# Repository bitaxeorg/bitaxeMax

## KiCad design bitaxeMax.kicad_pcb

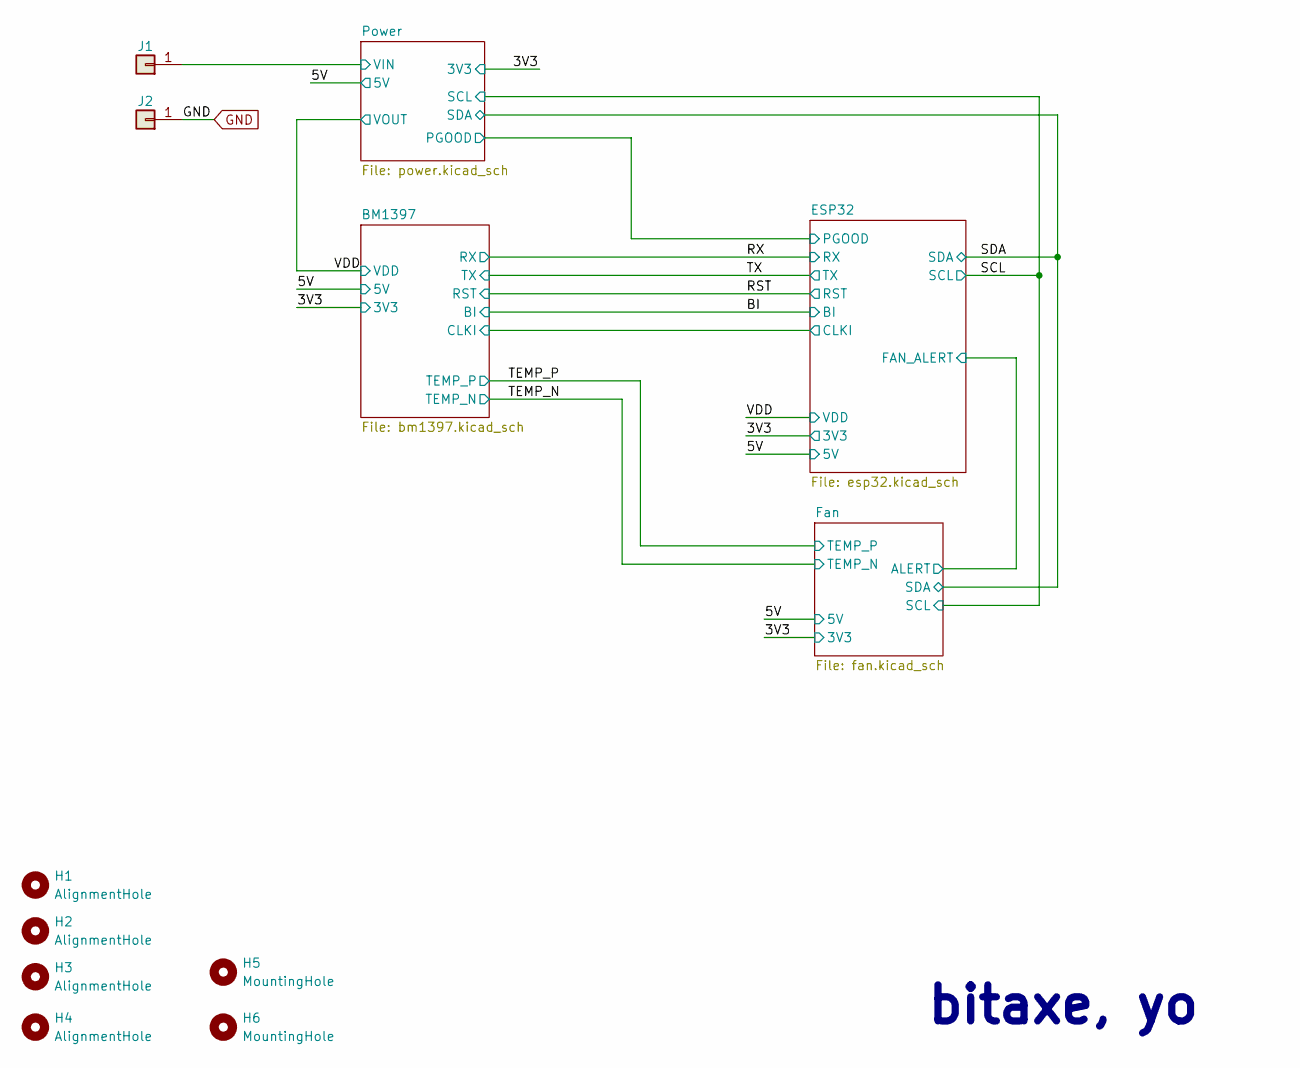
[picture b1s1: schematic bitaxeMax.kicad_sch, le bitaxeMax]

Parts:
H1, H2, H3, H4: AlignmentHole; MountingHole_2.2mm_M2
H5, H6: MountingHole; MountingHole_3.5mm
J1, J2: Conn_01x01; 63862-1; PARTNO 63862-1

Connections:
/Power/VIN: J1.1; also elsewhere on the board
GND: J2.1; also elsewhere on the board

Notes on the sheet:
bitaxe, yo

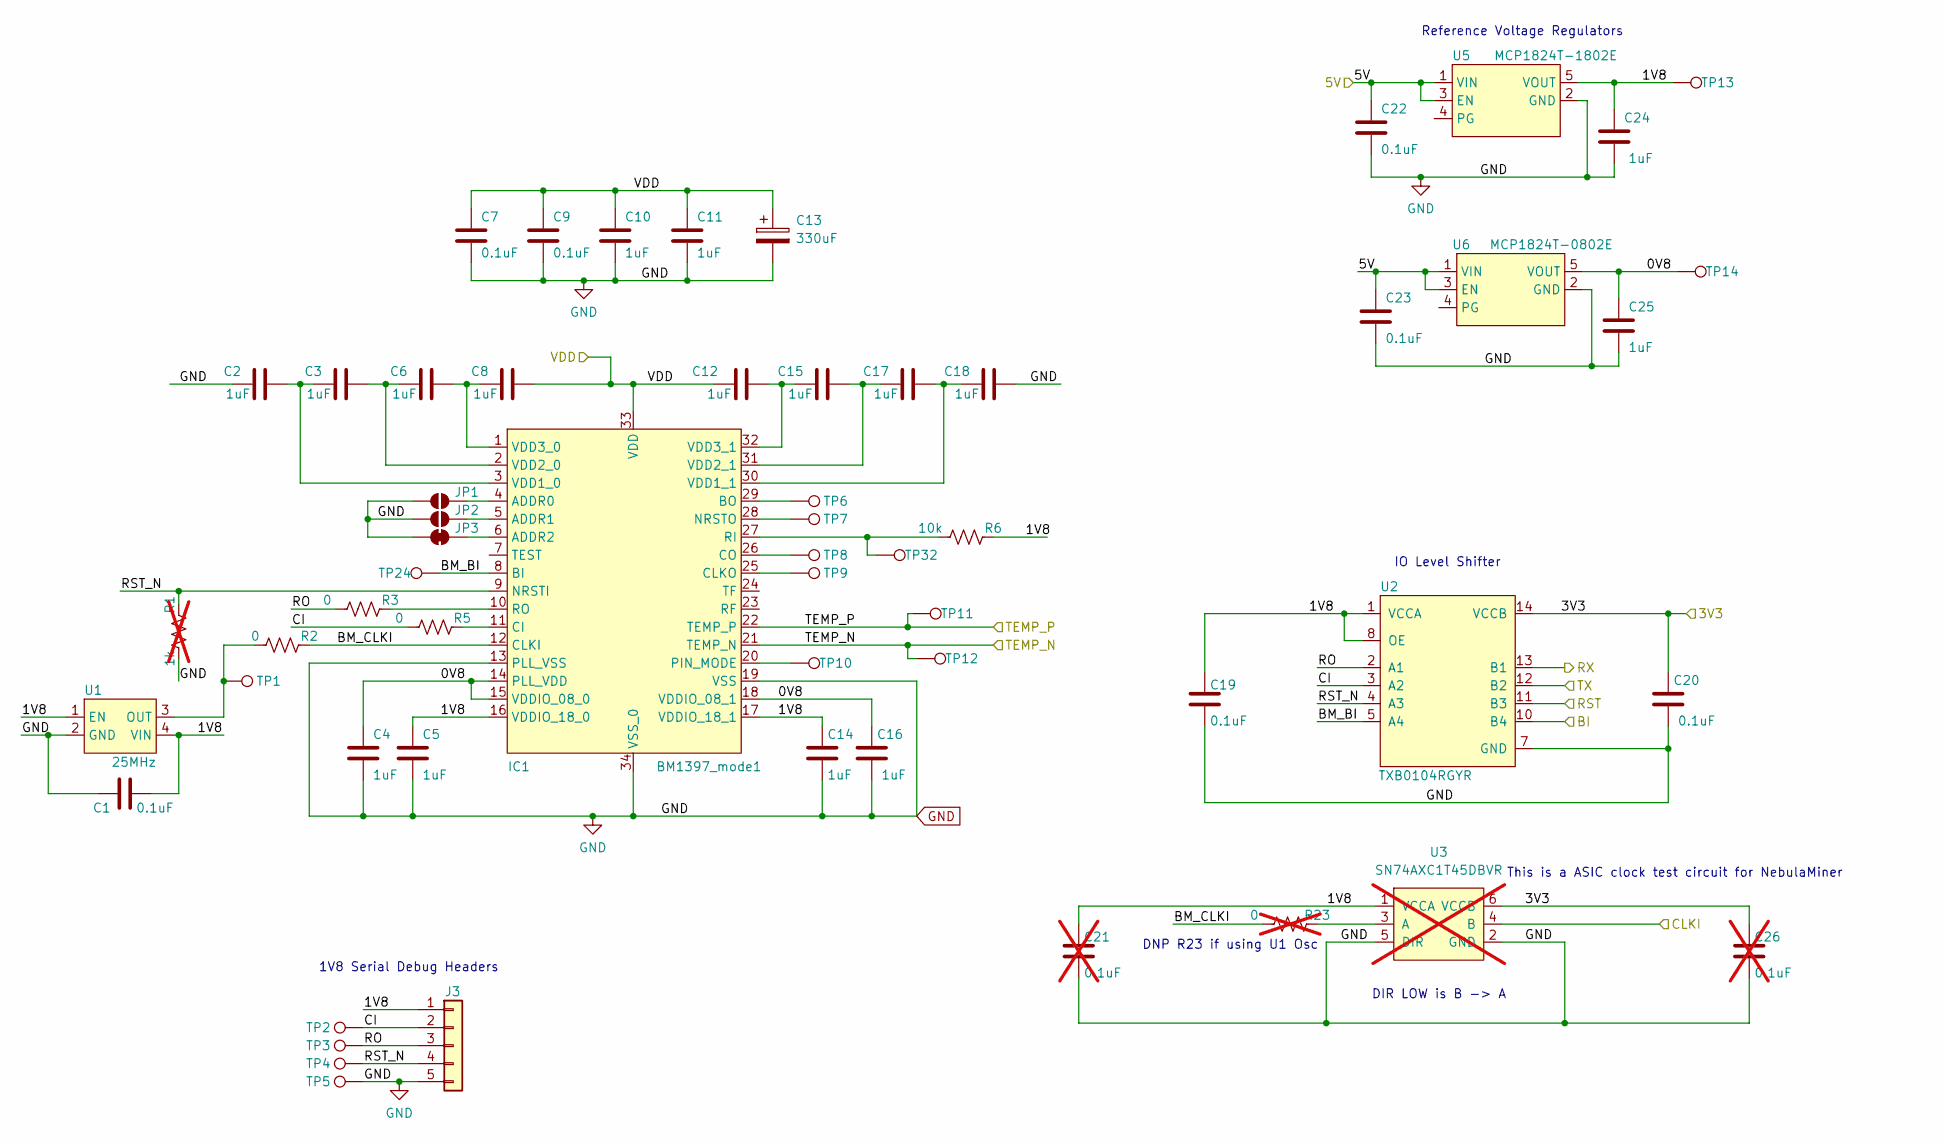
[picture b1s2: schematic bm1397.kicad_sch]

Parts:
C1, C7, C9, C19, C20, C22, C23: 0.1uF; C_0402_1005Metric; PARTNO 0402X104K100CT
C2, C3, C4, C5, C6, C8, C10, C11, C12, C14, C15, C16, C17, C18, C24, C25: 1uF; C_0402_1005Metric; PARTNO EMK105BJ105MV-F
C13: 330uF; CP_EIA-7343-31_Kemet-D_Pad2.25x2.55mm_HandSolder; PARTNO 293D337X9010E2TE3
C21, C26: 0.1uF; C_0402_1005Metric; PARTNO 0402X104K100CT; not fitted
IC1: BM1397_mode1; BM1397
J3: Conn_01x05; PinHeader_1x05_P2.54mm_Vertical
JP1, JP2: SolderJumper_2_Open; SolderJumper-2_P1.3mm_Open_RoundedPad1.0x1.5mm
JP3: SolderJumper_2_Bridged; SolderJumper-2_P1.3mm_Bridged2Bar_RoundedPad1.0x1.5mm
R1: 1k; R_0402_1005Metric; not fitted
R2, R3, R5: 0; R_0402_1005Metric; PARTNO RMCF0402ZT0R00
R6: 10k; R_0402_1005Metric; PARTNO RC0402JR-0710KL
R23: 0; R_0402_1005Metric; PARTNO RMCF0402ZT0R00; not fitted
TP1, TP2, TP3, TP4, TP5, TP6, TP7, TP8, TP9, TP10, TP11, TP12, TP13, TP14, TP24, TP32: TestPoint; TestPoint_Pad_D1.5mm
U1: 25MHz; O 25,0-JO32-B-1V3-1-T1-LF; PARTNO O 25,0-JO32-B-1V3-1-T1-LF
U2: TXB0104RGYR; TXB0104; PARTNO TXB0104RGYR
U3: SN74AXC1T45DBVR; SN74AXC1T45; PARTNO SN74AXC1T45DBVR; not fitted
U5: MCP1824T-1802E; SOT-23-5; PARTNO MCP1824T-1802E/OT
U6: MCP1824T-0802E; SOT-23-5; PARTNO MCP1824T-0802E/OT

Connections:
/3V3: C20.1, C26.1, U2.14 (VCCB), U3.6 (VCCB); also elsewhere on the board
/5V: C22.1, C23.1, U5.1 (VIN), U5.3 (EN), U6.1 (VIN), U6.3 (EN); also elsewhere on the board
/BI: U2.10 (B4); also elsewhere on the board
/BM1397/0V8: C4.1, C16.1, C25.1, IC1.14 (PLL_VDD), IC1.15 (VDDIO_08_0), IC1.18 (VDDIO_08_1), TP14.1, U6.5 (VOUT)
/BM1397/1V8: C1.2, C5.1, C14.1, C19.1, C21.1, C24.1, IC1.16 (VDDIO_18_0), IC1.17 (VDDIO_18_1), J3.1, R6.2, TP13.1, U1.1 (EN), U1.4 (VIN), U2.1 (VCCA), U2.8 (OE), U3.1 (VCCA), U5.5 (VOUT)
/BM1397/BM_BI: IC1.8 (BI), TP24.1, U2.5 (A4)
/BM1397/BM_CLKI: IC1.12 (CLKI), R2.2, R23.1
/BM1397/CI: J3.2, R5.1, TP2.1, U2.3 (A2)
/BM1397/CLKI: U3.4 (B); also elsewhere on the board
/BM1397/RO: J3.3, R3.1, TP3.1, U2.2 (A1)
/BM1397/RST_N: IC1.9 (NRSTI), J3.4, R1.2, TP4.1, U2.4 (A3)
/RST: U2.11 (B3); also elsewhere on the board
/RX: U2.13 (B1); also elsewhere on the board
/TEMP_N: IC1.21 (TEMP_N), TP12.1; also elsewhere on the board
/TEMP_P: IC1.22 (TEMP_P), TP11.1; also elsewhere on the board
/TX: U2.12 (B2); also elsewhere on the board
/VDD: C7.1, C8.2, C9.1, C10.1, C11.1, C12.1, C13.1, IC1.33 (VDD); also elsewhere on the board
GND: C1.1, C2.1, C4.2, C5.2, C7.2, C9.2, C10.2, C11.2, C13.2, C14.2, C16.2, C18.2, C19.2, C20.2, C21.2, C22.2, C23.2, C24.2, C25.2, C26.2, IC1.13 (PLL_VSS), IC1.19 (VSS), IC1.34 (VSS_0), J3.5, JP1.1 (A), JP2.1 (A), JP3.1 (A), R1.1, TP5.1, U1.2 (GND), U2.7 (GND), U2.15 (GND), U2.16 (GND), U2.17 (GND), U2.18 (GND), U2.19 (GND), U3.2 (GND), U3.5 (DIR), U5.2 (GND), U6.2 (GND); also elsewhere on the board
unnamed: C2.2, C3.1, IC1.3 (VDD1_0)
unnamed: C3.2, C6.1, IC1.2 (VDD2_0)
unnamed: C6.2, C8.1, IC1.1 (VDD3_0)
unnamed: C12.2, C15.1, IC1.32 (VDD3_1)
unnamed: C15.2, C17.1, IC1.31 (VDD2_1)
unnamed: C17.2, C18.1, IC1.30 (VDD1_1)
unnamed: IC1.4 (ADDR0), JP1.2 (B)
unnamed: IC1.5 (ADDR1), JP2.2 (B)
unnamed: IC1.6 (ADDR2), JP3.2 (B)
unnamed: IC1.10 (RO), R3.2
unnamed: IC1.11 (CI), R5.2
unnamed: IC1.20 (PIN_MODE), TP10.1
unnamed: IC1.25 (CLKO), TP9.1
unnamed: IC1.26 (CO), TP8.1
unnamed: IC1.27 (RI), R6.1, TP32.1
unnamed: IC1.28 (NRSTO), TP7.1
unnamed: IC1.29 (BO), TP6.1
unnamed: R2.1, TP1.1, U1.3 (OUT)
unnamed: R23.2, U3.3 (A)

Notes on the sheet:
1V8 Serial Debug Headers
Reference Voltage Regulators
DNP R23 if using U1 Osc
This is a ASIC clock test circuit for NebulaMiner
IO Level Shifter
DIR LOW is B -> A

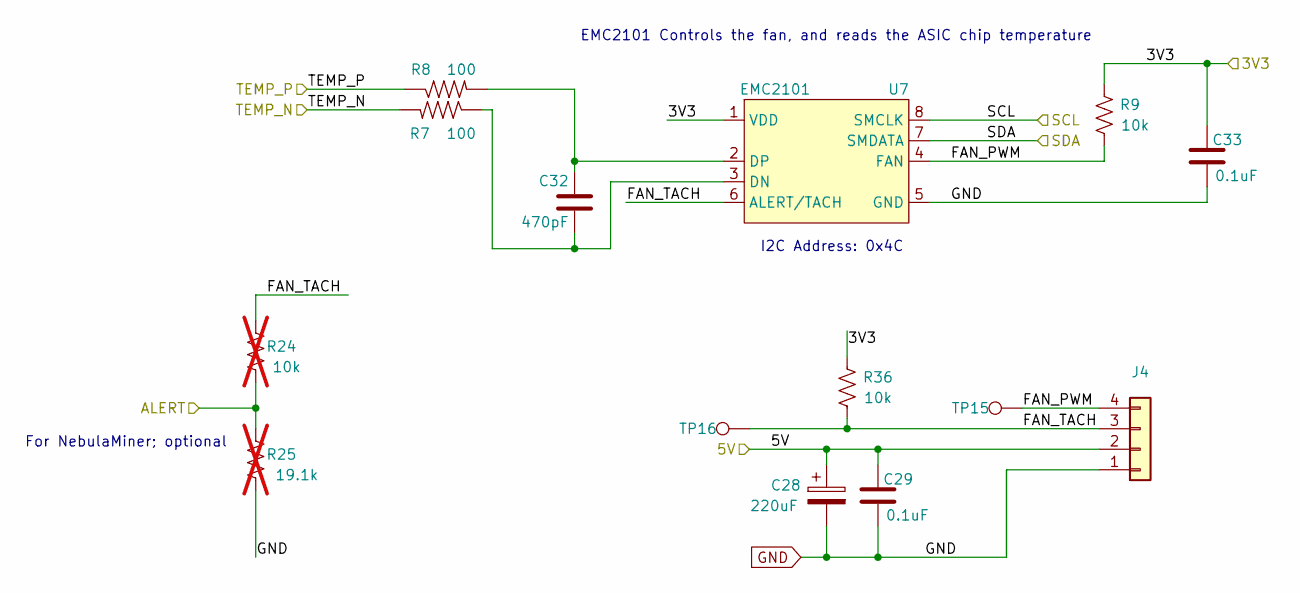
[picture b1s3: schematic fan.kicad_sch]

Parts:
C28: 220uF; CP_Elec_6.3x7.7; PARTNO 865080345012
C29, C33: 0.1uF; C_0402_1005Metric; PARTNO 0402X104K100CT
C32: 470pF; C_0402_1005Metric; PARTNO CL05B471KB5NNNC
J4: Conn_01x04; 470531000; PARTNO 0470531000
R7, R8: 100; R_0402_1005Metric; PARTNO RMCF0402FT100R
R9, R36: 10k; R_0402_1005Metric; PARTNO RC0402JR-0710KL
R24: 10k; R_0402_1005Metric; PARTNO RC0402JR-0710KL; not fitted
R25: 19.1k; R_0402_1005Metric; PARTNO RC0402FR-0719R1L; not fitted
TP15, TP16: TestPoint; TestPoint_Pad_D1.5mm
U7: EMC2101; TSSOP-8_3x3mm_P0.65mm; PARTNO EMC2101-R-ACZL-TR

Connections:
/3V3: C33.1, R9.2, R36.2, U7.1 (VDD); also elsewhere on the board
/5V: C28.1, C29.1, J4.2; also elsewhere on the board
/ESP32/FAN_ALERT: R24.1, R25.2; also elsewhere on the board
/Fan/FAN_PWM: J4.4, R9.1, TP15.1, U7.4 (FAN)
/Fan/FAN_TACH: J4.3, R24.2, R36.1, TP16.1, U7.6 (ALERT/TACH)
/SCL: U7.8 (SMCLK); also elsewhere on the board
/SDA: U7.7 (SMDATA); also elsewhere on the board
/TEMP_N: R7.2; also elsewhere on the board
/TEMP_P: R8.1; also elsewhere on the board
GND: C28.2, C29.2, C33.2, J4.1, R25.1, U7.5 (GND); also elsewhere on the board
unnamed: C32.1, R8.2, U7.2 (DP)
unnamed: C32.2, R7.1, U7.3 (DN)

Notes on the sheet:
For NebulaMiner; optional
EMC2101 Controls the fan, and reads the ASIC chip temperature
I2C Address: 0x4C

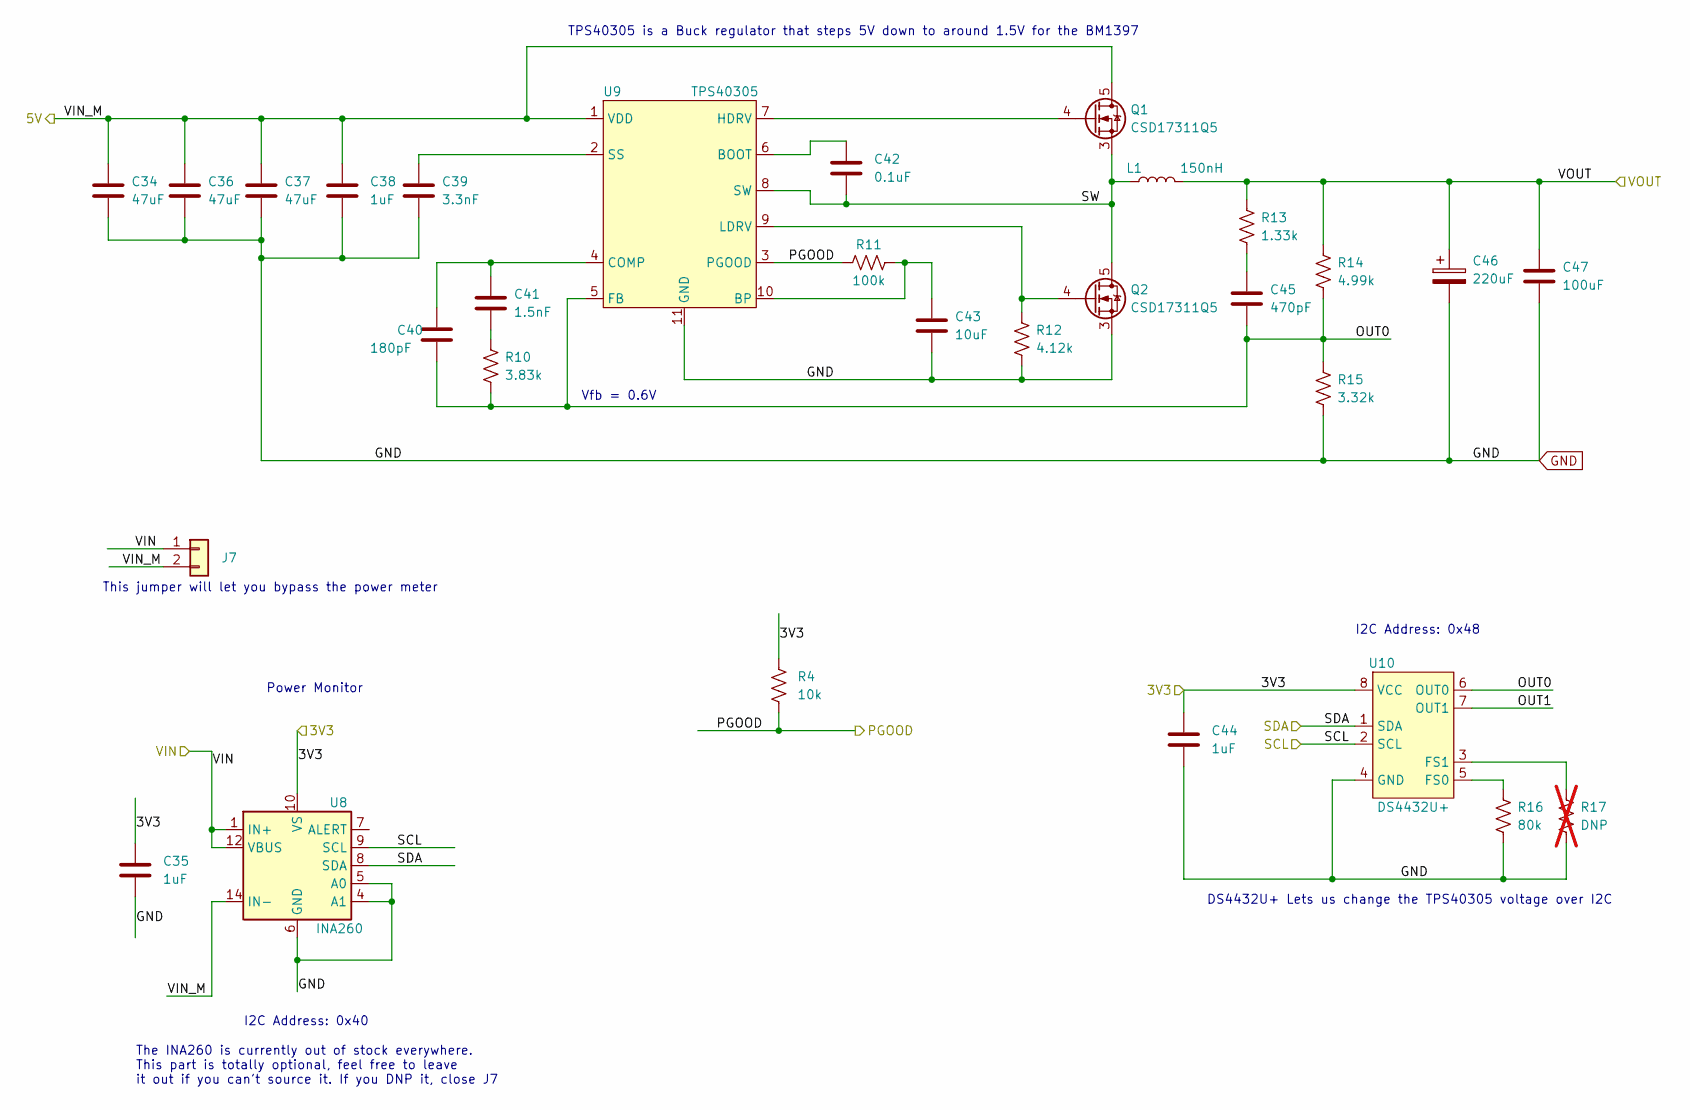
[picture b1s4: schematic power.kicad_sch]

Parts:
C34, C36, C37: 47uF; C_1210_3225Metric; PARTNO GRM32ER61C476KE15L
C35, C44: 1uF; C_0402_1005Metric; PARTNO EMK105BJ105MV-F
C38: 1uF; C_0805_2012Metric; PARTNO CL21B105KOFNNNG
C39: 3.3nF; C_0402_1005Metric; PARTNO CL05B332KB5NNNC
C40: 180pF; C_0805_2012Metric; PARTNO CC0805JRNPO9BN181
C41: 1.5nF; C_0805_2012Metric; PARTNO CC0805KRX7R9BB152
C42: 0.1uF; C_0402_1005Metric; PARTNO 0402X104K100CT
C43: 10uF; C_0805_2012Metric; PARTNO CL21A106KOQNNNE
C45: 470pF; C_0805_2012Metric; PARTNO 0805B471K500CT
C46: 220uF; CAP_2R5TPE220MAFB; PARTNO 2R5TPE220MAFB
C47: 100uF; C_1206_3216Metric; PARTNO C3216X5R0J107M160AB
J7: Conn_01x02; PinHeader_1x02_P2.54mm_Vertical
L1: 150nH; FP1005R1-R15-R; PARTNO FP1005R1-R15-R
Q1, Q2: CSD17311Q5; PARTNO CSD17311Q5
R4: 10k; R_0402_1005Metric; PARTNO RC0402JR-0710KL
R10: 3.83k; R_0402_1005Metric; PARTNO RC0402FR-073K83L
R11: 100k; R_0402_1005Metric; PARTNO RC0402JR-07100KL
R12: 4.12k; R_0402_1005Metric; PARTNO RMCF0402FT4K12
R13: 1.33k; R_0402_1005Metric; PARTNO RC0402FR-071K33L
R14: 4.99k; R_0402_1005Metric; PARTNO RC0402FR-074K99L
R15: 3.32k; R_0402_1005Metric; PARTNO RC0402FR-073K32L
R16: 80k; R_0402_1005Metric; PARTNO RC0402FR-0780K6L
R17: DNP; R_0402_1005Metric; not fitted
U8: INA260; TSSOP-16_4.4x5mm_P0.65mm; PARTNO INA260AIPWR
U9: TPS40305; PARTNO TPS40305DRCR
U10: DS4432U+; TSSOP-8_3x3mm_P0.65mm; PARTNO DS4432U+

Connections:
/3V3: C35.1, C44.1, R4.1, U8.10 (VS), U10.8 (VCC); also elsewhere on the board
/5V: C34.1, C36.1, C37.1, C38.1, J7.2, Q1.5 (D), U8.14 (IN-), U8.15 (IN-), U8.16 (IN-), U9.1 (VDD); also elsewhere on the board
/Power/OUT0: C40.2, C45.2, R10.2, R14.2, R15.1, U9.5 (FB), U10.6 (OUT0)
/Power/OUT1: U10.7 (OUT1)
/Power/PGOOD: R4.2, R11.1, U9.3 (PGOOD); also elsewhere on the board
/Power/SW: C42.2, L1.1, Q1.1, Q1.2, Q1.3 (S), Q2.5 (D), U9.8 (SW)
/Power/VIN: J7.1, U8.1 (IN+), U8.2 (IN+), U8.3 (IN+), U8.12 (VBUS); also elsewhere on the board
/SCL: U8.9 (SCL), U10.2 (SCL); also elsewhere on the board
/SDA: U8.8 (SDA), U10.1 (SDA); also elsewhere on the board
/VDD: C46.1, C47.1, L1.2, R13.1, R14.1; also elsewhere on the board
GND: C34.2, C35.2, C36.2, C37.2, C38.2, C39.2, C43.2, C44.2, C46.2, C47.2, Q2.1, Q2.2, Q2.3 (S), R12.2, R15.2, R16.2, R17.2, U8.4 (A1), U8.5 (A0), U8.6 (GND), U8.11 (GND), U9.11 (GND), U10.4 (GND); also elsewhere on the board
unnamed: C39.1, U9.2 (SS)
unnamed: C40.1, C41.1, U9.4 (COMP)
unnamed: C41.2, R10.1
unnamed: C42.1, U9.6 (BOOT)
unnamed: C43.1, R11.2, U9.10 (BP)
unnamed: C45.1, R13.2
unnamed: Q1.4 (G), U9.7 (HDRV)
unnamed: Q2.4 (G), R12.1, U9.9 (LDRV)
unnamed: R16.1, U10.5 (FS0)
unnamed: R17.1, U10.3 (FS1)

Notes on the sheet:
DS4432U+ Lets us change the TPS40305 voltage over I2C
I2C Address: 0x48
The INA260 is currently out of stock everywhere. This part is totally optional, feel free to leave it out if you can't source it. If you DNP it, close J7
Power Monitor
TPS40305 is a Buck regulator that steps 5V down to around 1.5V for the BM1397
I2C Address: 0x40
Vfb = 0.6V
This jumper will let you bypass the power meter

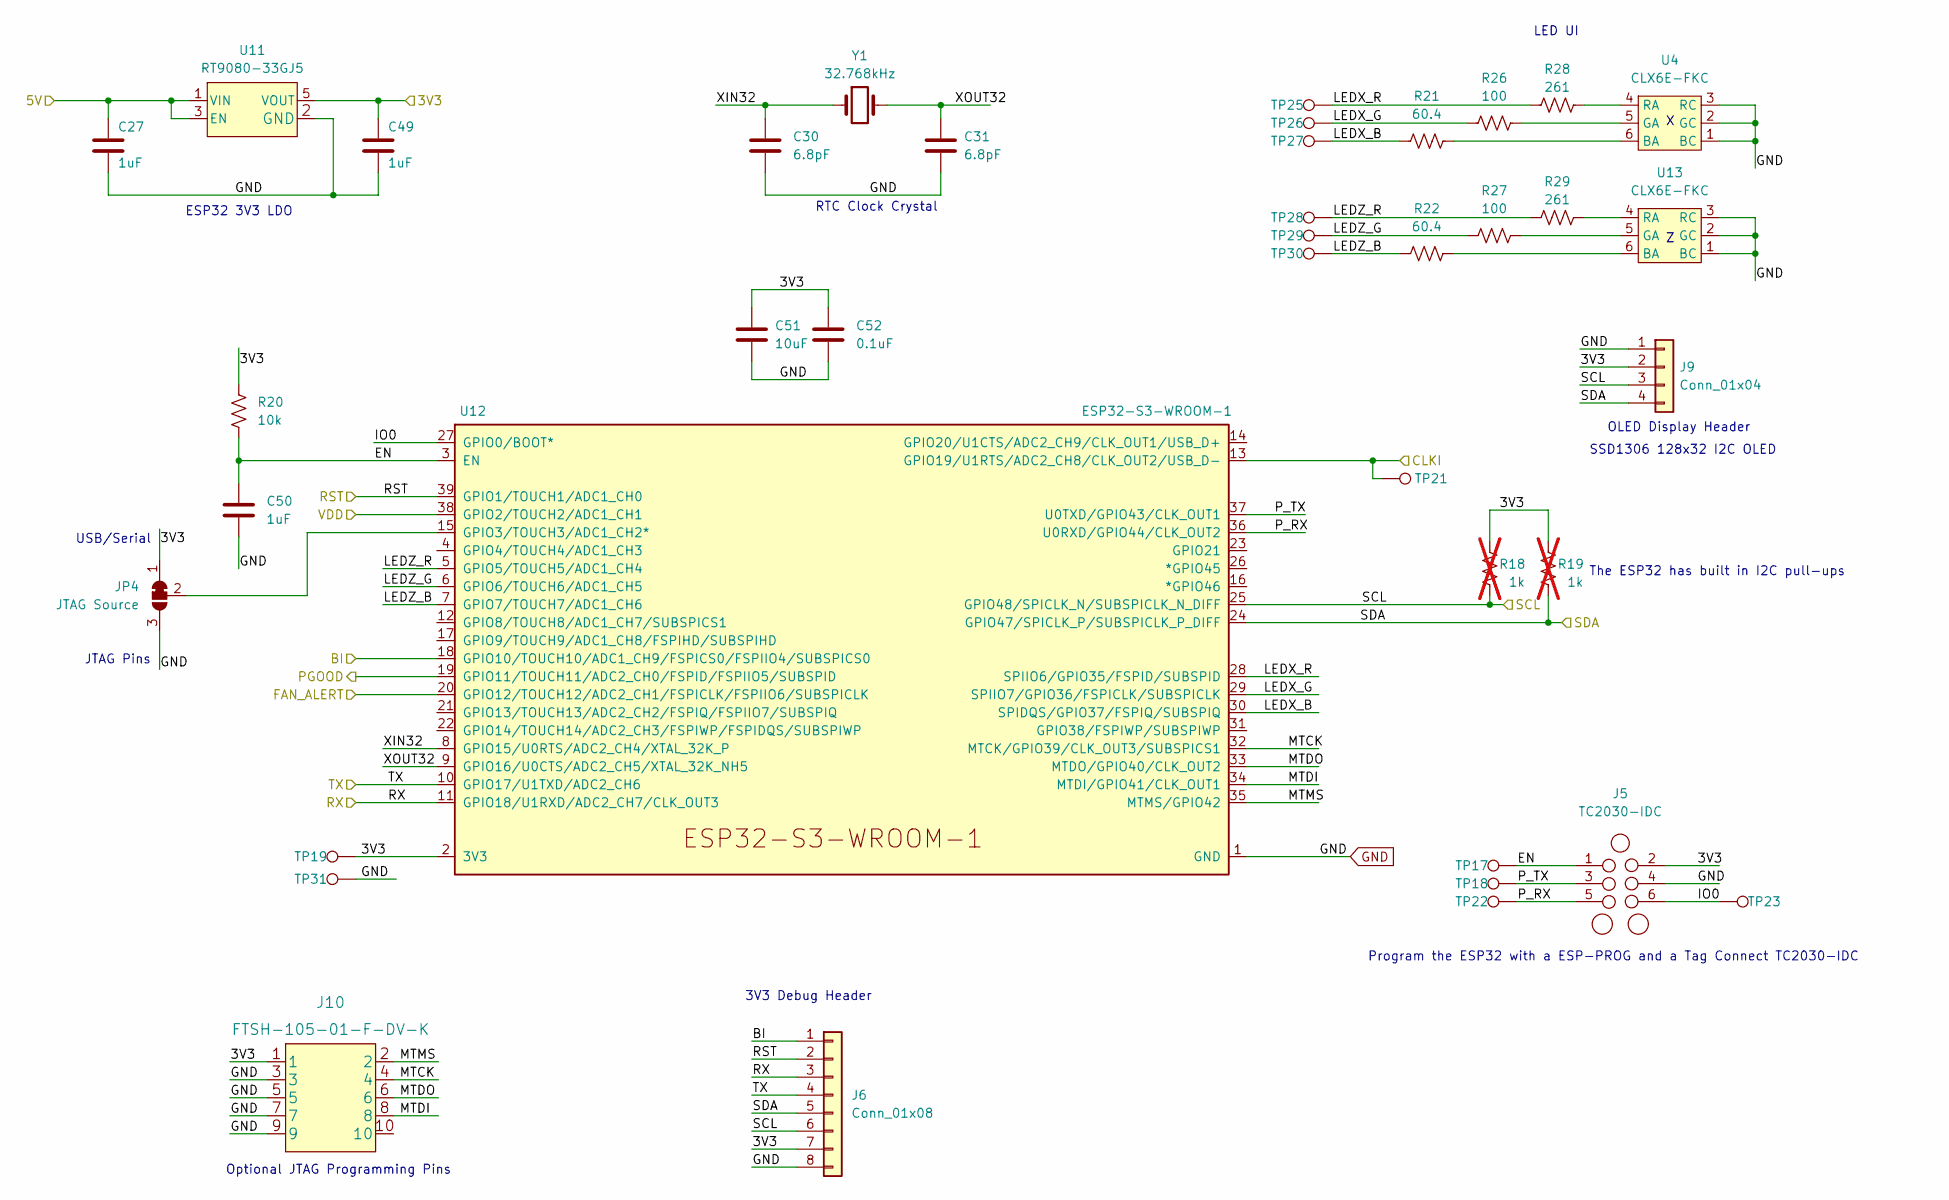
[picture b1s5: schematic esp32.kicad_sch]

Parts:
C27, C49, C50: 1uF; C_0402_1005Metric; PARTNO EMK105BJ105MV-F
C30, C31: 6.8pF; C_0402_1005Metric; PARTNO C0402C689C5GAC7867
C51: 10uF; C_0805_2012Metric; PARTNO CL21A106KOQNNNE
C52: 0.1uF; C_0402_1005Metric; PARTNO 0402X104K100CT
J5: TC2030-IDC; Tag-Connect_TC2030-IDC-NL_2x03_P1.27mm_Vertical
J6: Conn_01x08; PinHeader_1x08_P2.54mm_Vertical
J9: Conn_01x04; PinHeader_1x04_P2.54mm_Vertical
J10: FTSH-105-01-F-DV-K; PARTNO FTSH-105-01-F-DV-K
JP4: JTAG Source; SolderJumper-3_P1.3mm_Bridged2Bar12_Pad1.0x1.5mm
R18, R19: 1k; R_0402_1005Metric; not fitted
R20: 10k; R_0402_1005Metric; PARTNO RC0402JR-0710KL
R21, R22: 60.4; R_0402_1005Metric; PARTNO RC0402FR-0760R4L
R26, R27: 100; R_0402_1005Metric; PARTNO RMCF0402FT100R
R28, R29: 261; R_0402_1005Metric; PARTNO RC0402FR-07261RL
TP17, TP18, TP19, TP21, TP22, TP23, TP25, TP26, TP27, TP28, TP29, TP30, TP31: TestPoint; TestPoint_Pad_D1.5mm
U4, U13: CLX6E-FKC; CLX6E-FKC-CH1M1D1BB7C3D3; PARTNO CLX6E-FKC-CH1M1D1BB7C3D3
U11: RT9080-33GJ5; PARTNO RT9080-33GJ5
U12: ESP32-S3-WROOM-1; PARTNO ESP32-S3-WROOM-1-N16R8
Y1: 32.768kHz; SC32S-7PF20PPM; PARTNO SC32S-7PF20PPM

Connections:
/3V3: C49.1, C51.1, C52.1, J5.2, J6.7, J9.2, J10.1, JP4.1 (A), R18.2, R19.2, R20.1, TP19.1, U11.5 (VOUT), U12.2 (3V3); also elsewhere on the board
/5V: C27.1, U11.1 (VIN), U11.3 (EN); also elsewhere on the board
/BI: J6.1, U12.18 (GPIO10/TOUCH10/ADC1_CH9/FSPICS0/FSPIIO4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); also elsewhere on the board
/BM1397/CLKI: TP21.1, U12.13 (GPIO19/U1RTS/ADC2_CH8/CLK_OUT2/USB_D-); also elsewhere on the board
/ESP32/EN: C50.1, J5.1, R20.2, TP17.1, U12.3 (EN)
/ESP32/FAN_ALERT: U12.20 (GPIO12/TOUCH12/ADC2_CH1/FSPICLK/FSPIIO6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); also elsewhere on the board
/ESP32/IO0: J5.6, TP23.1, U12.27 (GPIO0/BOOT*)
/ESP32/LEDX_B: R21.1, TP27.1, U12.30 (SPIDQS/GPIO37/FSPIQ/SUBSPIQ)
/ESP32/LEDX_G: R26.1, TP26.1, U12.29 (SPIIO7/GPIO36/FSPICLK/SUBSPICLK)
/ESP32/LEDX_R: R28.1, TP25.1, U12.28 (SPIIO6/GPIO35/FSPID/SUBSPID)
/ESP32/LEDZ_B: R22.1, TP30.1, U12.7 (GPIO7/TOUCH7/ADC1_CH6)
/ESP32/LEDZ_G: R27.1, TP29.1, U12.6 (GPIO6/TOUCH6/ADC1_CH5)
/ESP32/LEDZ_R: R29.1, TP28.1, U12.5 (GPIO5/TOUCH5/ADC1_CH4)
/ESP32/MTCK: J10.4, U12.32 (MTCK/GPIO39/CLK_OUT3/SUBSPICS1)
/ESP32/MTDI: J10.8, U12.34 (MTDI/GPIO41/CLK_OUT1)
/ESP32/MTDO: J10.6, U12.33 (MTDO/GPIO40/CLK_OUT2)
/ESP32/MTMS: J10.2, U12.35 (MTMS/GPIO42)
/ESP32/P_RX: J5.5, TP22.1, U12.36 (U0RXD/GPIO44/CLK_OUT2)
/ESP32/P_TX: J5.3, TP18.1, U12.37 (U0TXD/GPIO43/CLK_OUT1)
/ESP32/XIN32: C30.1, U12.8 (GPIO15/U0RTS/ADC2_CH4/XTAL_32K_P), Y1.1
/ESP32/XOUT32: C31.1, U12.9 (GPIO16/U0CTS/ADC2_CH5/XTAL_32K_NH5), Y1.2
/Power/PGOOD: U12.19 (GPIO11/TOUCH11/ADC2_CH0/FSPID/FSPIIO5/S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); also elsewhere on the board
/RST: J6.2, U12.39 (GPIO1/TOUCH1/ADC1_CH0); also elsewhere on the board
/RX: J6.3, U12.11 (GPIO18/U1RXD/ADC2_CH7/CLK_OUT3); also elsewhere on the board
/SCL: J6.6, J9.3, R18.1, U12.25 (GPIO48/SPICLK_N/SUBSPICLK_N_DIFF); also elsewhere on the board
/SDA: J6.5, J9.4, R19.1, U12.24 (GPIO47/SPICLK_P/SUBSPICLK_P_DIFF); also elsewhere on the board
/TX: J6.4, U12.10 (GPIO17/U1TXD/ADC2_CH6); also elsewhere on the board
/VDD: U12.38 (GPIO2/TOUCH2/ADC1_CH1); also elsewhere on the board
GND: C27.2, C30.2, C31.2, C49.2, C50.2, C51.2, C52.2, J5.4, J6.8, J9.1, J10.3, J10.5, J10.7, J10.9, JP4.3 (B), TP31.1, U4.1 (BC), U4.2 (GC), U4.3 (RC), U11.2 (GND), U12.1 (GND), U12.40 (GND), U12.41 (GND), U13.1 (BC), U13.2 (GC), U13.3 (RC); also elsewhere on the board
unnamed: R21.2, U4.6 (BA)
unnamed: R22.2, U13.6 (BA)
unnamed: R26.2, U4.5 (GA)
unnamed: R27.2, U13.5 (GA)
unnamed: R28.2, U4.4 (RA)
unnamed: R29.2, U13.4 (RA)
unnamed: JP4.2 (C), U12.15 (GPIO3/TOUCH3/ADC1_CH2*)

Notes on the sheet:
RTC Clock Crystal
JTAG Pins
ESP32 3V3 LDO
Program the ESP32 with a ESP-PROG and a Tag Connect TC2030-IDC
The ESP32 has built in I2C pull-ups
3V3 Debug Header
Optional JTAG Programming Pins
SSD1306 128x32 I2C OLED
LED UI
OLED Display Header
USB/Serial

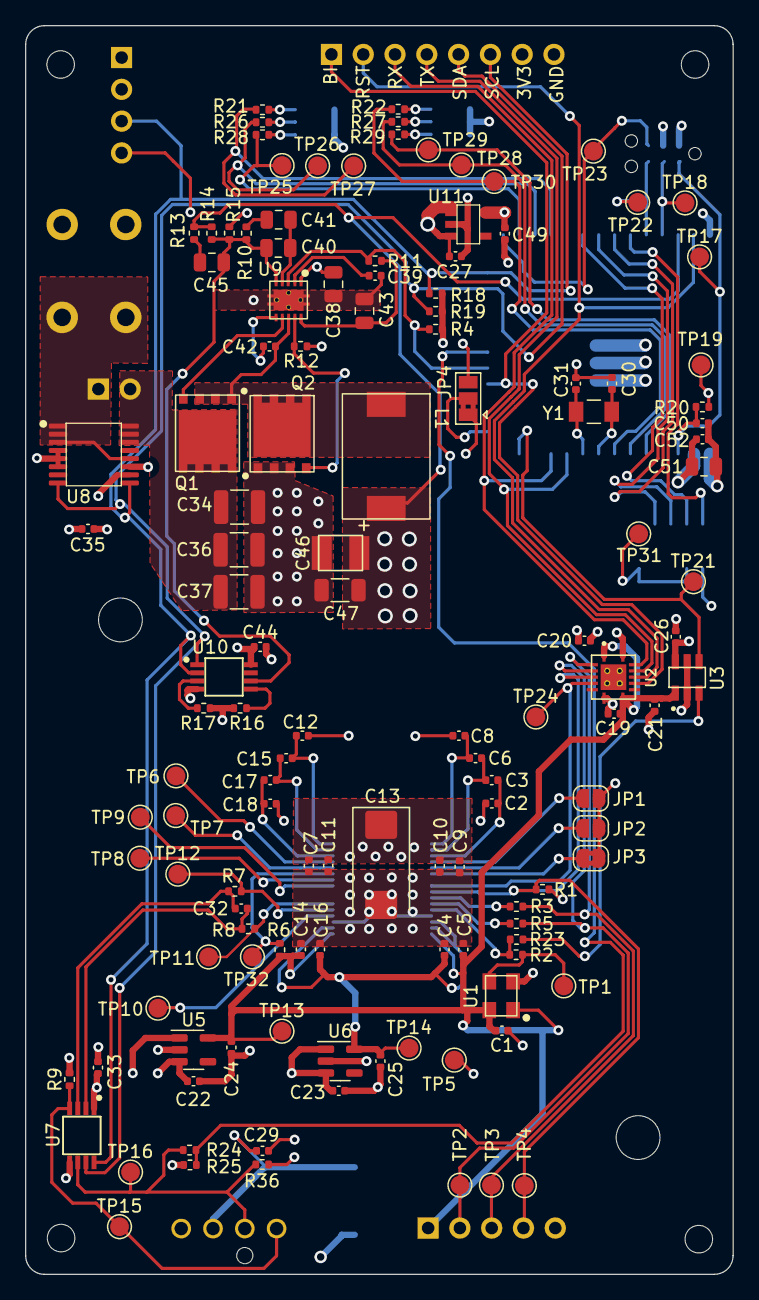
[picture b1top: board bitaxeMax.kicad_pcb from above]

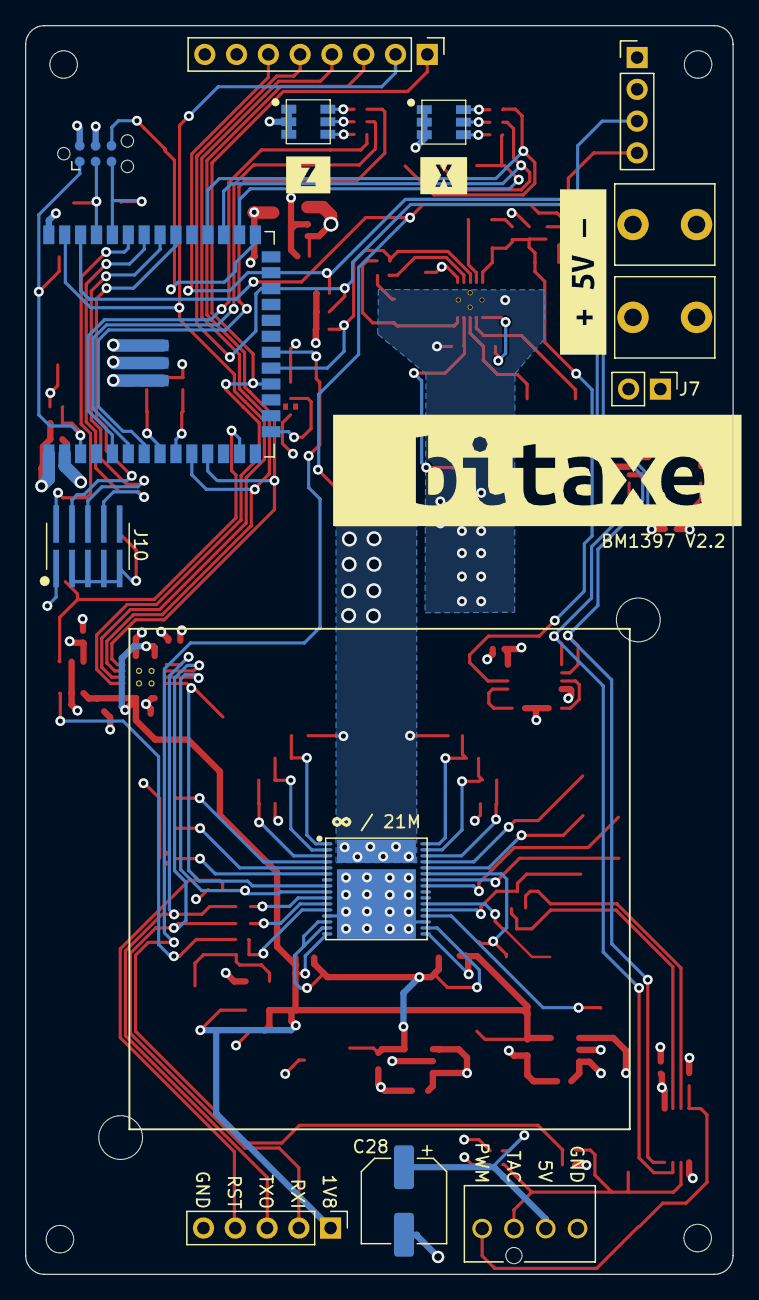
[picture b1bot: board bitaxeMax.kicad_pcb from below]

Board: 4 copper layers, 56.5 x 99.8 mm, 153 parts (18 on the bottom side), 81 nets.

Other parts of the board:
kibuzzard-63D74789: G***; kibuzzard-63D74789
kibuzzard-6387EEBE: G***; kibuzzard-6387EEBE
kibuzzard-6387EECB: G***; kibuzzard-6387EECB
kibuzzard-6392B1E5: G***; kibuzzard-6392B1E5

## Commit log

2025-01-04 Update LICENSE
2025-01-04 Create LICENSE
